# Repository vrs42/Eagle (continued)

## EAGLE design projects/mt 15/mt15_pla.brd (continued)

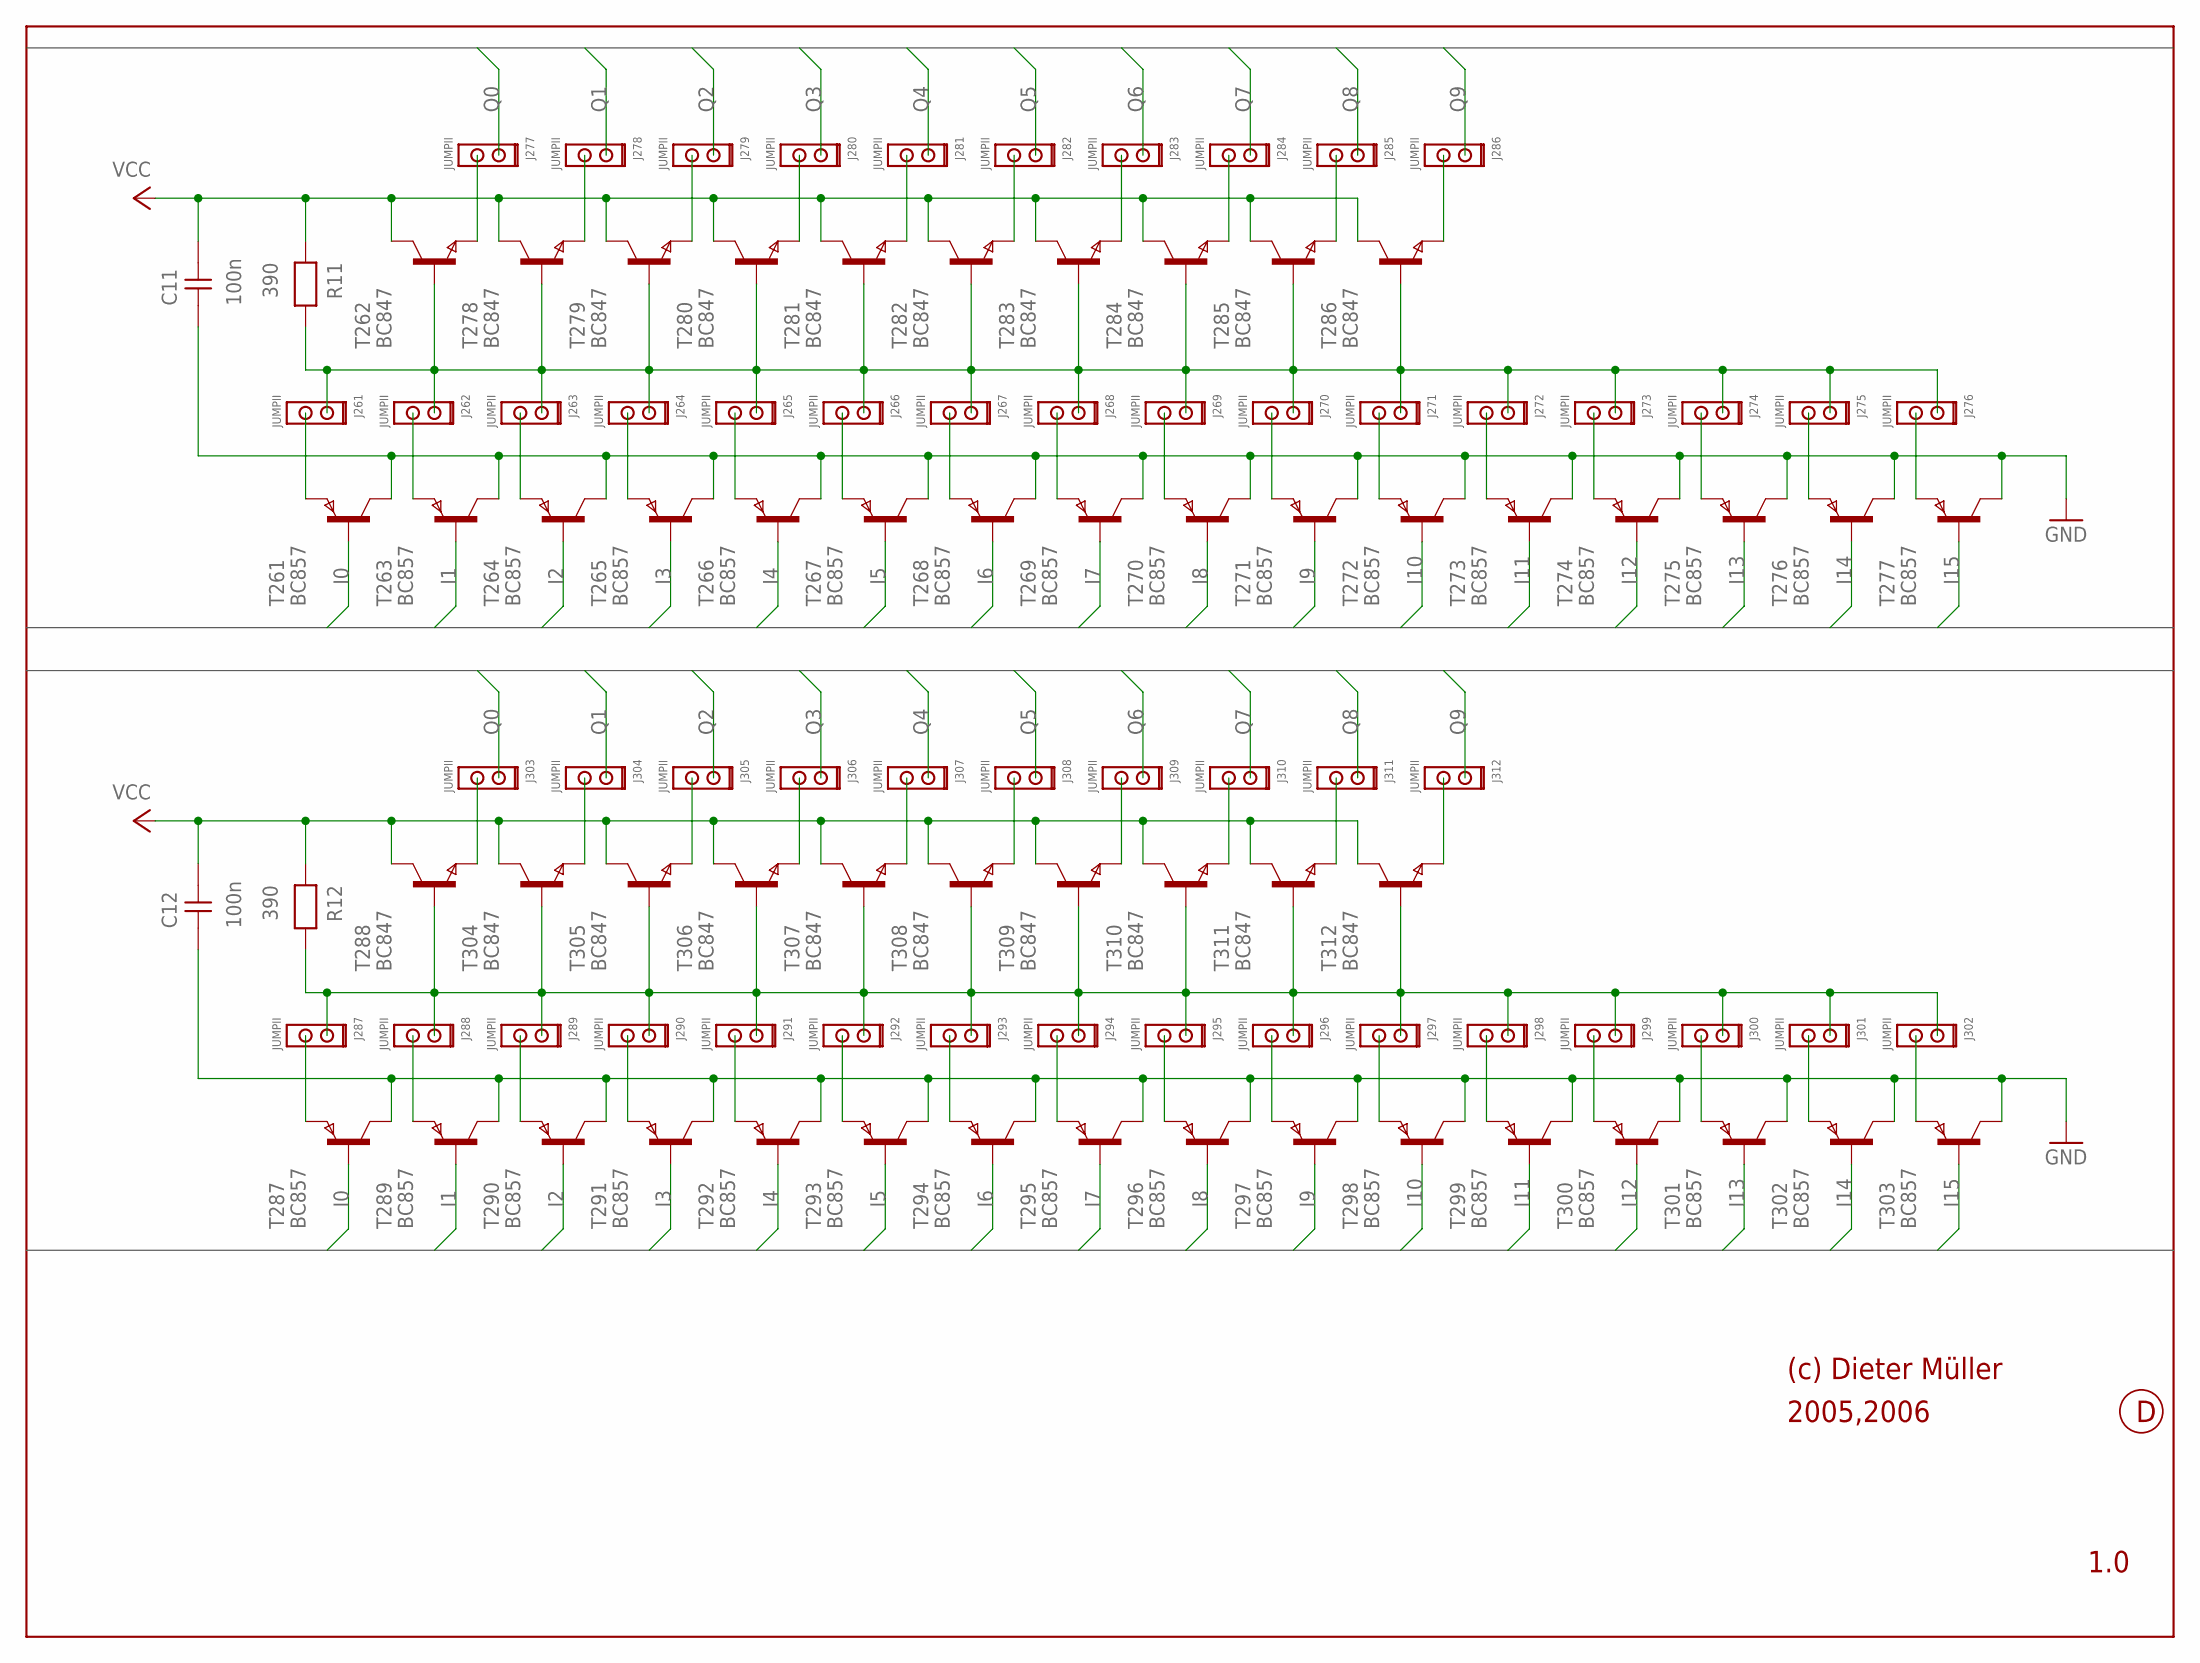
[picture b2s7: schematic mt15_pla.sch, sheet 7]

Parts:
C11, C12: 100n; 0204
J261, J262, J263, J264, J265, J266, J267, J268, J269, J270, J271, J272, J273, J274, J275, J276, J277, J278, J279, J280, J281, J282, J283, J284, J285, J286, J287, J288, J289, J290, J291, J292, J293, J294, J295, J296, J297, J298, J299, J300, J301, J302, J303, J304, J305, J306, J307, J308, J309, J310, J311, J312: JUMPII
R11, R12: 390; 0204
T261, T263, T264, T265, T266, T267, T268, T269, T270, T271, T272, T273, T274, T275, T276, T277, T287, T289, T290, T291, T292, T293, T294, T295, T296, T297, T298, T299, T300, T301, T302, T303: BC857; SOT-23
T262, T278, T279, T280, T281, T282, T283, T284, T285, T286, T288, T304, T305, T306, T307, T308, T309, T310, T311, T312: BC847; SOT-23

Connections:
GND: C11.1, C12.1, T261.3 (C), T263.3 (C), T264.3 (C), T265.3 (C), T266.3 (C), T267.3 (C), T268.3 (C), T269.3 (C), T270.3 (C), T271.3 (C), T272.3 (C), T273.3 (C), T274.3 (C), T275.3 (C), T276.3 (C), T277.3 (C), T287.3 (C), T289.3 (C), T290.3 (C), T291.3 (C), T292.3 (C), T293.3 (C), T294.3 (C), T295.3 (C), T296.3 (C), T297.3 (C), T298.3 (C), T299.3 (C), T300.3 (C), T301.3 (C), T302.3 (C), T303.3 (C); also elsewhere on the board
I0: T261.2 (B), T287.2 (B); also elsewhere on the board
I1: T263.2 (B), T289.2 (B); also elsewhere on the board
I2: T264.2 (B), T290.2 (B); also elsewhere on the board
I3: T265.2 (B), T291.2 (B); also elsewhere on the board
I4: T266.2 (B), T292.2 (B); also elsewhere on the board
I5: T267.2 (B), T293.2 (B); also elsewhere on the board
I6: T268.2 (B), T294.2 (B); also elsewhere on the board
I7: T269.2 (B), T295.2 (B); also elsewhere on the board
I8: T270.2 (B), T296.2 (B); also elsewhere on the board
I9: T271.2 (B), T297.2 (B); also elsewhere on the board
I10: T272.2 (B), T298.2 (B); also elsewhere on the board
I11: T273.2 (B), T299.2 (B); also elsewhere on the board
I12: T274.2 (B), T300.2 (B); also elsewhere on the board
I13: T275.2 (B), T301.2 (B); also elsewhere on the board
I14: T276.2 (B), T302.2 (B); also elsewhere on the board
I15: T277.2 (B), T303.2 (B); also elsewhere on the board
unnamed: J261.2, T261.1 (E)
unnamed: J262.2, T263.1 (E)
unnamed: J263.2, T264.1 (E)
unnamed: J261.1, J262.1, J263.1, J264.1, J265.1, J266.1, J267.1, J268.1, J269.1, J270.1, J271.1, J272.1, J273.1, J274.1, J275.1, J276.1, R11.2, T262.2 (B), T278.2 (B), T279.2 (B), T280.2 (B), T281.2 (B), T282.2 (B), T283.2 (B), T284.2 (B), T285.2 (B), T286.2 (B)
unnamed: J276.2, T277.1 (E)
unnamed: J275.2, T276.1 (E)
unnamed: J274.2, T275.1 (E)
unnamed: J273.2, T274.1 (E)
unnamed: J272.2, T273.1 (E)
unnamed: J266.2, T267.1 (E)
unnamed: J265.2, T266.1 (E)
unnamed: J264.2, T265.1 (E)
unnamed: J267.2, T268.1 (E)
unnamed: J268.2, T269.1 (E)
unnamed: J269.2, T270.1 (E)
unnamed: J270.2, T271.1 (E)
unnamed: J271.2, T272.1 (E)
unnamed: J286.2, T286.1 (E)
unnamed: J277.2, T262.1 (E)
unnamed: J278.2, T278.1 (E)
unnamed: J279.2, T279.1 (E)
unnamed: J280.2, T280.1 (E)
unnamed: J281.2, T281.1 (E)
unnamed: J282.2, T282.1 (E)
unnamed: J283.2, T283.1 (E)
unnamed: J284.2, T284.1 (E)
unnamed: J285.2, T285.1 (E)
unnamed: J287.2, T287.1 (E)
unnamed: J288.2, T289.1 (E)
unnamed: J289.2, T290.1 (E)
unnamed: J287.1, J288.1, J289.1, J290.1, J291.1, J292.1, J293.1, J294.1, J295.1, J296.1, J297.1, J298.1, J299.1, J300.1, J301.1, J302.1, R12.2, T288.2 (B), T304.2 (B), T305.2 (B), T306.2 (B), T307.2 (B), T308.2 (B), T309.2 (B), T310.2 (B), T311.2 (B), T312.2 (B)
unnamed: J302.2, T303.1 (E)
unnamed: J301.2, T302.1 (E)
unnamed: J300.2, T301.1 (E)
unnamed: J299.2, T300.1 (E)
unnamed: J298.2, T299.1 (E)
unnamed: J292.2, T293.1 (E)
unnamed: J291.2, T292.1 (E)
unnamed: J290.2, T291.1 (E)
unnamed: J293.2, T294.1 (E)
unnamed: J294.2, T295.1 (E)
unnamed: J295.2, T296.1 (E)
unnamed: J296.2, T297.1 (E)
unnamed: J297.2, T298.1 (E)
unnamed: J312.2, T312.1 (E)
unnamed: J303.2, T288.1 (E)
unnamed: J304.2, T304.1 (E)
unnamed: J305.2, T305.1 (E)
unnamed: J306.2, T306.1 (E)
unnamed: J307.2, T307.1 (E)
unnamed: J308.2, T308.1 (E)
unnamed: J309.2, T309.1 (E)
unnamed: J310.2, T310.1 (E)
unnamed: J311.2, T311.1 (E)
Q0: J277.1, J303.1; also elsewhere on the board
Q1: J278.1, J304.1; also elsewhere on the board
Q2: J279.1, J305.1; also elsewhere on the board
Q3: J280.1, J306.1; also elsewhere on the board
Q4: J281.1, J307.1; also elsewhere on the board
Q5: J282.1, J308.1; also elsewhere on the board
Q6: J283.1, J309.1; also elsewhere on the board
Q7: J284.1, J310.1; also elsewhere on the board
Q8: J285.1, J311.1; also elsewhere on the board
Q9: J286.1, J312.1; also elsewhere on the board
VCC: C11.2, C12.2, R11.1, R12.1, T262.3 (C), T278.3 (C), T279.3 (C), T280.3 (C), T281.3 (C), T282.3 (C), T283.3 (C), T284.3 (C), T285.3 (C), T286.3 (C), T288.3 (C), T304.3 (C), T305.3 (C), T306.3 (C), T307.3 (C), T308.3 (C), T309.3 (C), T310.3 (C), T311.3 (C), T312.3 (C); also elsewhere on the board

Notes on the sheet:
(c) Dieter Müller
2005,2006
1.0

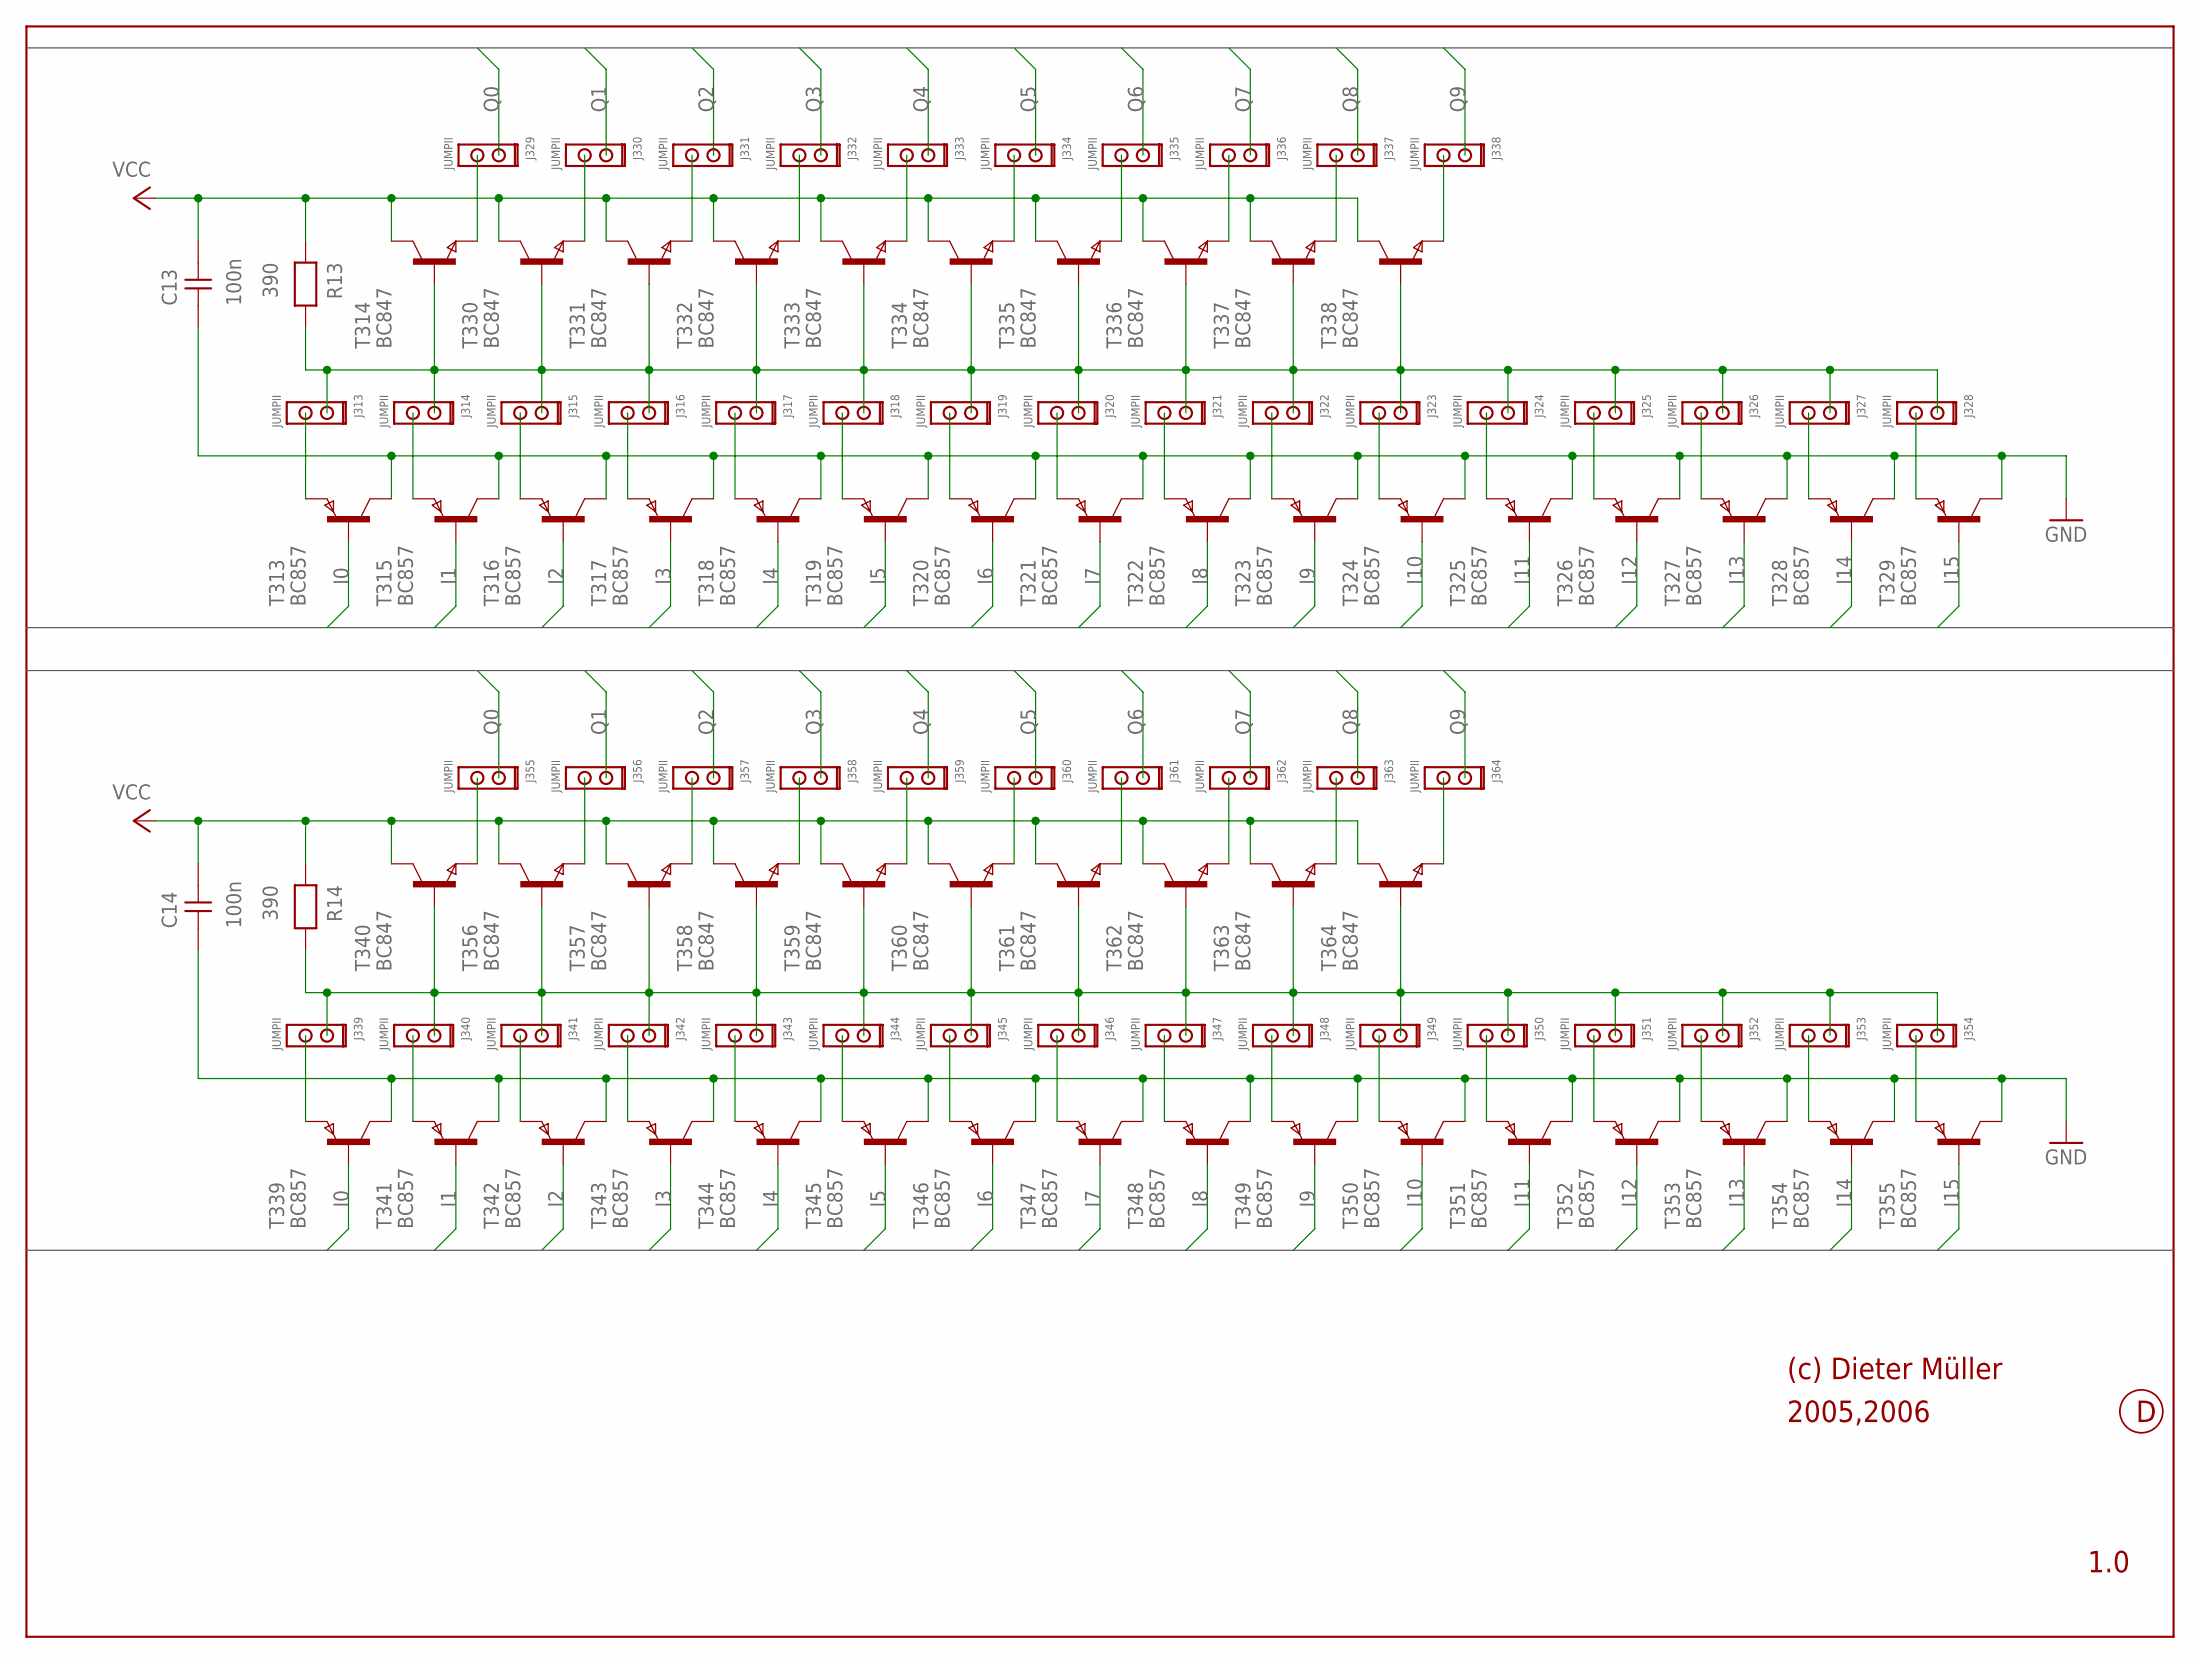
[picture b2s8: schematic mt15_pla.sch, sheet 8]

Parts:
C13, C14: 100n; 0204
J313, J314, J315, J316, J317, J318, J319, J320, J321, J322, J323, J324, J325, J326, J327, J328, J329, J330, J331, J332, J333, J334, J335, J336, J337, J338, J339, J340, J341, J342, J343, J344, J345, J346, J347, J348, J349, J350, J351, J352, J353, J354, J355, J356, J357, J358, J359, J360, J361, J362, J363, J364: JUMPII
R13, R14: 390; 0204
T313, T315, T316, T317, T318, T319, T320, T321, T322, T323, T324, T325, T326, T327, T328, T329, T339, T341, T342, T343, T344, T345, T346, T347, T348, T349, T350, T351, T352, T353, T354, T355: BC857; SOT-23
T314, T330, T331, T332, T333, T334, T335, T336, T337, T338, T340, T356, T357, T358, T359, T360, T361, T362, T363, T364: BC847; SOT-23

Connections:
GND: C13.1, C14.1, T313.3 (C), T315.3 (C), T316.3 (C), T317.3 (C), T318.3 (C), T319.3 (C), T320.3 (C), T321.3 (C), T322.3 (C), T323.3 (C), T324.3 (C), T325.3 (C), T326.3 (C), T327.3 (C), T328.3 (C), T329.3 (C), T339.3 (C), T341.3 (C), T342.3 (C), T343.3 (C), T344.3 (C), T345.3 (C), T346.3 (C), T347.3 (C), T348.3 (C), T349.3 (C), T350.3 (C), T351.3 (C), T352.3 (C), T353.3 (C), T354.3 (C), T355.3 (C); also elsewhere on the board
I0: T313.2 (B), T339.2 (B); also elsewhere on the board
I1: T315.2 (B), T341.2 (B); also elsewhere on the board
I2: T316.2 (B), T342.2 (B); also elsewhere on the board
I3: T317.2 (B), T343.2 (B); also elsewhere on the board
I4: T318.2 (B), T344.2 (B); also elsewhere on the board
I5: T319.2 (B), T345.2 (B); also elsewhere on the board
I6: T320.2 (B), T346.2 (B); also elsewhere on the board
I7: T321.2 (B), T347.2 (B); also elsewhere on the board
I8: T322.2 (B), T348.2 (B); also elsewhere on the board
I9: T323.2 (B), T349.2 (B); also elsewhere on the board
I10: T324.2 (B), T350.2 (B); also elsewhere on the board
I11: T325.2 (B), T351.2 (B); also elsewhere on the board
I12: T326.2 (B), T352.2 (B); also elsewhere on the board
I13: T327.2 (B), T353.2 (B); also elsewhere on the board
I14: T328.2 (B), T354.2 (B); also elsewhere on the board
I15: T329.2 (B), T355.2 (B); also elsewhere on the board
unnamed: J313.2, T313.1 (E)
unnamed: J314.2, T315.1 (E)
unnamed: J315.2, T316.1 (E)
unnamed: J313.1, J314.1, J315.1, J316.1, J317.1, J318.1, J319.1, J320.1, J321.1, J322.1, J323.1, J324.1, J325.1, J326.1, J327.1, J328.1, R13.2, T314.2 (B), T330.2 (B), T331.2 (B), T332.2 (B), T333.2 (B), T334.2 (B), T335.2 (B), T336.2 (B), T337.2 (B), T338.2 (B)
unnamed: J328.2, T329.1 (E)
unnamed: J327.2, T328.1 (E)
unnamed: J326.2, T327.1 (E)
unnamed: J325.2, T326.1 (E)
unnamed: J324.2, T325.1 (E)
unnamed: J318.2, T319.1 (E)
unnamed: J317.2, T318.1 (E)
unnamed: J316.2, T317.1 (E)
unnamed: J319.2, T320.1 (E)
unnamed: J320.2, T321.1 (E)
unnamed: J321.2, T322.1 (E)
unnamed: J322.2, T323.1 (E)
unnamed: J323.2, T324.1 (E)
unnamed: J338.2, T338.1 (E)
unnamed: J329.2, T314.1 (E)
unnamed: J330.2, T330.1 (E)
unnamed: J331.2, T331.1 (E)
unnamed: J332.2, T332.1 (E)
unnamed: J333.2, T333.1 (E)
unnamed: J334.2, T334.1 (E)
unnamed: J335.2, T335.1 (E)
unnamed: J336.2, T336.1 (E)
unnamed: J337.2, T337.1 (E)
unnamed: J339.2, T339.1 (E)
unnamed: J340.2, T341.1 (E)
unnamed: J341.2, T342.1 (E)
unnamed: J339.1, J340.1, J341.1, J342.1, J343.1, J344.1, J345.1, J346.1, J347.1, J348.1, J349.1, J350.1, J351.1, J352.1, J353.1, J354.1, R14.2, T340.2 (B), T356.2 (B), T357.2 (B), T358.2 (B), T359.2 (B), T360.2 (B), T361.2 (B), T362.2 (B), T363.2 (B), T364.2 (B)
unnamed: J354.2, T355.1 (E)
unnamed: J353.2, T354.1 (E)
unnamed: J352.2, T353.1 (E)
unnamed: J351.2, T352.1 (E)
unnamed: J350.2, T351.1 (E)
unnamed: J344.2, T345.1 (E)
unnamed: J343.2, T344.1 (E)
unnamed: J342.2, T343.1 (E)
unnamed: J345.2, T346.1 (E)
unnamed: J346.2, T347.1 (E)
unnamed: J347.2, T348.1 (E)
unnamed: J348.2, T349.1 (E)
unnamed: J349.2, T350.1 (E)
unnamed: J364.2, T364.1 (E)
unnamed: J355.2, T340.1 (E)
unnamed: J356.2, T356.1 (E)
unnamed: J357.2, T357.1 (E)
unnamed: J358.2, T358.1 (E)
unnamed: J359.2, T359.1 (E)
unnamed: J360.2, T360.1 (E)
unnamed: J361.2, T361.1 (E)
unnamed: J362.2, T362.1 (E)
unnamed: J363.2, T363.1 (E)
Q0: J329.1, J355.1; also elsewhere on the board
Q1: J330.1, J356.1; also elsewhere on the board
Q2: J331.1, J357.1; also elsewhere on the board
Q3: J332.1, J358.1; also elsewhere on the board
Q4: J333.1, J359.1; also elsewhere on the board
Q5: J334.1, J360.1; also elsewhere on the board
Q6: J335.1, J361.1; also elsewhere on the board
Q7: J336.1, J362.1; also elsewhere on the board
Q8: J337.1, J363.1; also elsewhere on the board
Q9: J338.1, J364.1; also elsewhere on the board
VCC: C13.2, C14.2, R13.1, R14.1, T314.3 (C), T330.3 (C), T331.3 (C), T332.3 (C), T333.3 (C), T334.3 (C), T335.3 (C), T336.3 (C), T337.3 (C), T338.3 (C), T340.3 (C), T356.3 (C), T357.3 (C), T358.3 (C), T359.3 (C), T360.3 (C), T361.3 (C), T362.3 (C), T363.3 (C), T364.3 (C); also elsewhere on the board

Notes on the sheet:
(c) Dieter Müller
2005,2006
1.0

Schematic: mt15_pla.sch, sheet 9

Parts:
C15, C16: 100n; 0204
J365, J366, J367, J368, J369, J370, J371, J372, J373, J374, J375, J376, J377, J378, J379, J380, J381, J382, J383, J384, J385, J386, J387, J388, J389, J390, J391, J392, J393, J394, J395, J396, J397, J398, J399, J400, J401, J402, J403, J404, J405, J406, J407, J408, J409, J410, J411, J412, J413, J414, J415, J416: JUMPII
R15, R16: 390; 0204
T365, T367, T368, T369, T370, T371, T372, T373, T374, T375, T376, T377, T378, T379, T380, T381, T391, T393, T394, T395, T396, T397, T398, T399, T400, T401, T402, T403, T404, T405, T406, T407: BC857; SOT-23
T366, T382, T383, T384, T385, T386, T387, T388, T389, T390, T392, T408, T409, T410, T411, T412, T413, T414, T415, T416: BC847; SOT-23

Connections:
GND: C15.1, C16.1, T365.3 (C), T367.3 (C), T368.3 (C), T369.3 (C), T370.3 (C), T371.3 (C), T372.3 (C), T373.3 (C), T374.3 (C), T375.3 (C), T376.3 (C), T377.3 (C), T378.3 (C), T379.3 (C), T380.3 (C), T381.3 (C), T391.3 (C), T393.3 (C), T394.3 (C), T395.3 (C), T396.3 (C), T397.3 (C), T398.3 (C), T399.3 (C), T400.3 (C), T401.3 (C), T402.3 (C), T403.3 (C), T404.3 (C), T405.3 (C), T406.3 (C), T407.3 (C); also elsewhere on the board
I0: T365.2 (B), T391.2 (B); also elsewhere on the board
I1: T367.2 (B), T393.2 (B); also elsewhere on the board
I2: T368.2 (B), T394.2 (B); also elsewhere on the board
I3: T369.2 (B), T395.2 (B); also elsewhere on the board
I4: T370.2 (B), T396.2 (B); also elsewhere on the board
I5: T371.2 (B), T397.2 (B); also elsewhere on the board
I6: T372.2 (B), T398.2 (B); also elsewhere on the board
I7: T373.2 (B), T399.2 (B); also elsewhere on the board
I8: T374.2 (B), T400.2 (B); also elsewhere on the board
I9: T375.2 (B), T401.2 (B); also elsewhere on the board
I10: T376.2 (B), T402.2 (B); also elsewhere on the board
I11: T377.2 (B), T403.2 (B); also elsewhere on the board
I12: T378.2 (B), T404.2 (B); also elsewhere on the board
I13: T379.2 (B), T405.2 (B); also elsewhere on the board
I14: T380.2 (B), T406.2 (B); also elsewhere on the board
I15: T381.2 (B), T407.2 (B); also elsewhere on the board
unnamed: J365.2, T365.1 (E)
unnamed: J366.2, T367.1 (E)
unnamed: J367.2, T368.1 (E)
unnamed: J365.1, J366.1, J367.1, J368.1, J369.1, J370.1, J371.1, J372.1, J373.1, J374.1, J375.1, J376.1, J377.1, J378.1, J379.1, J380.1, R15.2, T366.2 (B), T382.2 (B), T383.2 (B), T384.2 (B), T385.2 (B), T386.2 (B), T387.2 (B), T388.2 (B), T389.2 (B), T390.2 (B)
unnamed: J380.2, T381.1 (E)
unnamed: J379.2, T380.1 (E)
unnamed: J378.2, T379.1 (E)
unnamed: J377.2, T378.1 (E)
unnamed: J376.2, T377.1 (E)
unnamed: J370.2, T371.1 (E)
unnamed: J369.2, T370.1 (E)
unnamed: J368.2, T369.1 (E)
unnamed: J371.2, T372.1 (E)
unnamed: J372.2, T373.1 (E)
unnamed: J373.2, T374.1 (E)
unnamed: J374.2, T375.1 (E)
unnamed: J375.2, T376.1 (E)
unnamed: J390.2, T390.1 (E)
unnamed: J381.2, T366.1 (E)
unnamed: J382.2, T382.1 (E)
unnamed: J383.2, T383.1 (E)
unnamed: J384.2, T384.1 (E)
unnamed: J385.2, T385.1 (E)
unnamed: J386.2, T386.1 (E)
unnamed: J387.2, T387.1 (E)
unnamed: J388.2, T388.1 (E)
unnamed: J389.2, T389.1 (E)
unnamed: J391.2, T391.1 (E)
unnamed: J392.2, T393.1 (E)
unnamed: J393.2, T394.1 (E)
unnamed: J391.1, J392.1, J393.1, J394.1, J395.1, J396.1, J397.1, J398.1, J399.1, J400.1, J401.1, J402.1, J403.1, J404.1, J405.1, J406.1, R16.2, T392.2 (B), T408.2 (B), T409.2 (B), T410.2 (B), T411.2 (B), T412.2 (B), T413.2 (B), T414.2 (B), T415.2 (B), T416.2 (B)
unnamed: J406.2, T407.1 (E)
unnamed: J405.2, T406.1 (E)
unnamed: J404.2, T405.1 (E)
unnamed: J403.2, T404.1 (E)
unnamed: J402.2, T403.1 (E)
unnamed: J396.2, T397.1 (E)
unnamed: J395.2, T396.1 (E)
unnamed: J394.2, T395.1 (E)
unnamed: J397.2, T398.1 (E)
unnamed: J398.2, T399.1 (E)
unnamed: J399.2, T400.1 (E)
unnamed: J400.2, T401.1 (E)
unnamed: J401.2, T402.1 (E)
unnamed: J416.2, T416.1 (E)
unnamed: J407.2, T392.1 (E)
unnamed: J408.2, T408.1 (E)
unnamed: J409.2, T409.1 (E)
unnamed: J410.2, T410.1 (E)
unnamed: J411.2, T411.1 (E)
unnamed: J412.2, T412.1 (E)
unnamed: J413.2, T413.1 (E)
unnamed: J414.2, T414.1 (E)
unnamed: J415.2, T415.1 (E)
Q0: J381.1, J407.1; also elsewhere on the board
Q1: J382.1, J408.1; also elsewhere on the board
Q2: J383.1, J409.1; also elsewhere on the board
Q3: J384.1, J410.1; also elsewhere on the board
Q4: J385.1, J411.1; also elsewhere on the board
Q5: J386.1, J412.1; also elsewhere on the board
Q6: J387.1, J413.1; also elsewhere on the board
Q7: J388.1, J414.1; also elsewhere on the board
Q8: J389.1, J415.1; also elsewhere on the board
Q9: J390.1, J416.1; also elsewhere on the board
VCC: C15.2, C16.2, R15.1, R16.1, T366.3 (C), T382.3 (C), T383.3 (C), T384.3 (C), T385.3 (C), T386.3 (C), T387.3 (C), T388.3 (C), T389.3 (C), T390.3 (C), T392.3 (C), T408.3 (C), T409.3 (C), T410.3 (C), T411.3 (C), T412.3 (C), T413.3 (C), T414.3 (C), T415.3 (C), T416.3 (C); also elsewhere on the board

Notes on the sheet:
(c) Dieter Müller
2005,2006
1.0

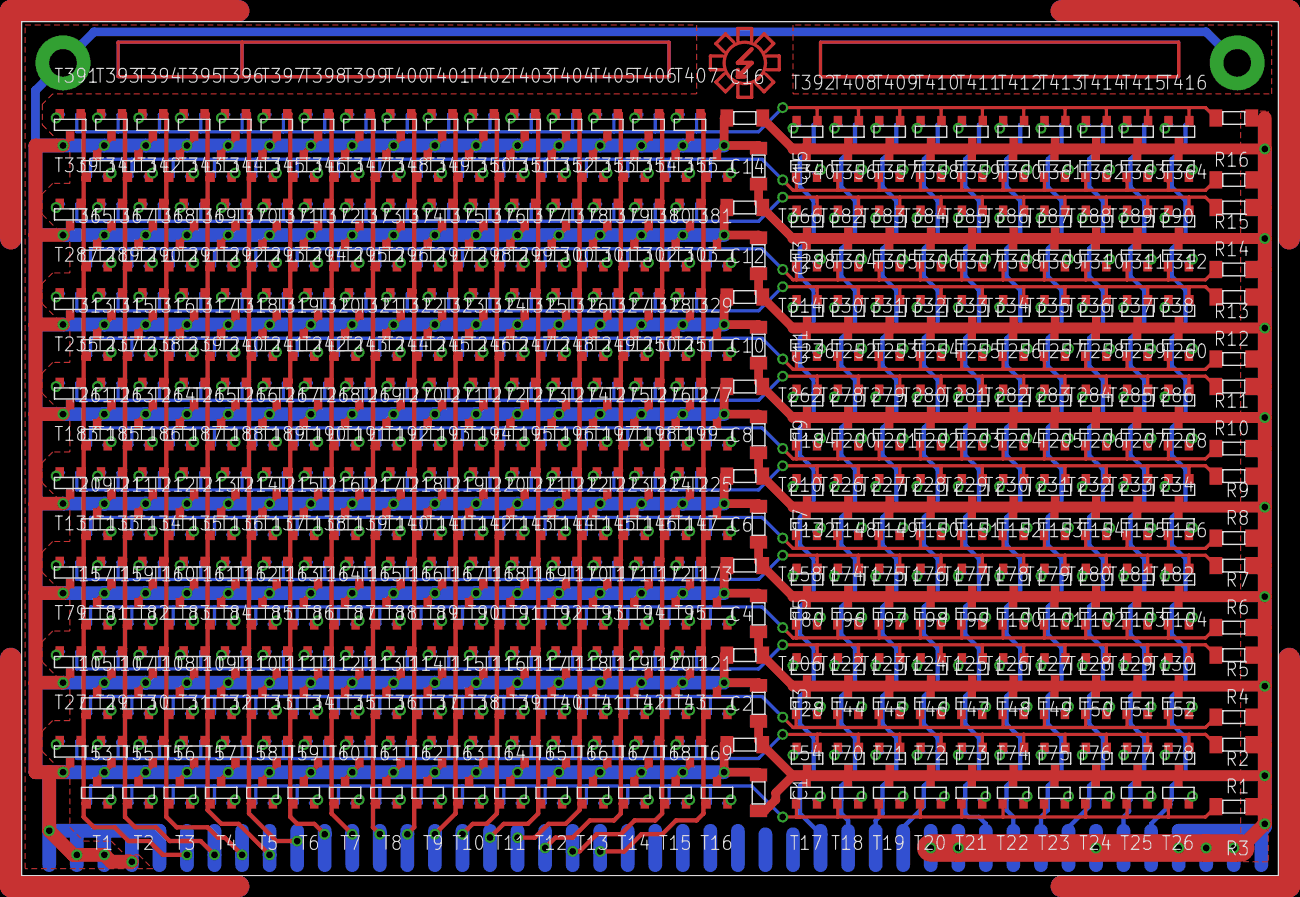
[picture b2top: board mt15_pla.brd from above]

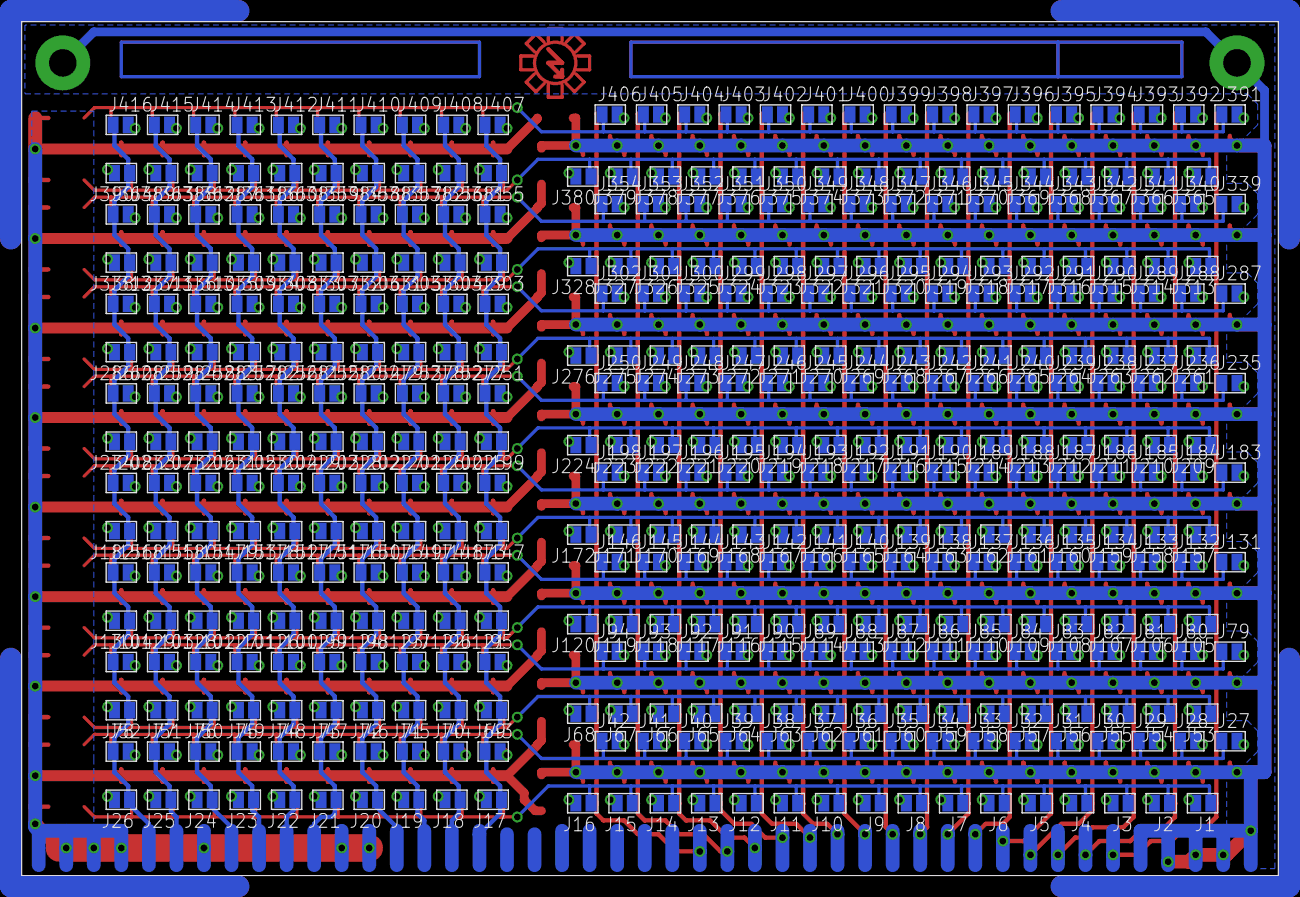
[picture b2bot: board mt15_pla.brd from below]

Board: 2 copper layers, 115.9 x 78.7 mm, 865 parts (416 on the bottom side), 460 nets.

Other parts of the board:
U$41: T1

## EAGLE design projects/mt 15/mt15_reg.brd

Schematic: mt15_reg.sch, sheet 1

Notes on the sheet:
(c) Dieter Müller
2005,2006
1.0
Free for hobby use, but probably not free of errors.
Provided as is , without any warranty or support.
Good luck.
ACC
L_ACC
I_ACC
ALU_A
O_ACC
I_PC
L_PC
O_PC
ALU_PC
L_T0
L_T1
ALU_Q0
ALU_Q1
OD_T0
OA_T0
OQ_T0
OD_T1
OA_T1
OQ_T1
Q_OUT
A_OUT
D_OUT
Address
Data
ALU
Note:
Blue marked lines
are outside of this module.
Green marked lines
work as control lines
(load or output_enable)
Block diagram
Supply voltage is 2.5V. Please change/modify resistors for other supply voltages.
For more details about the registers, consult the last page of this schematic (Page 6).

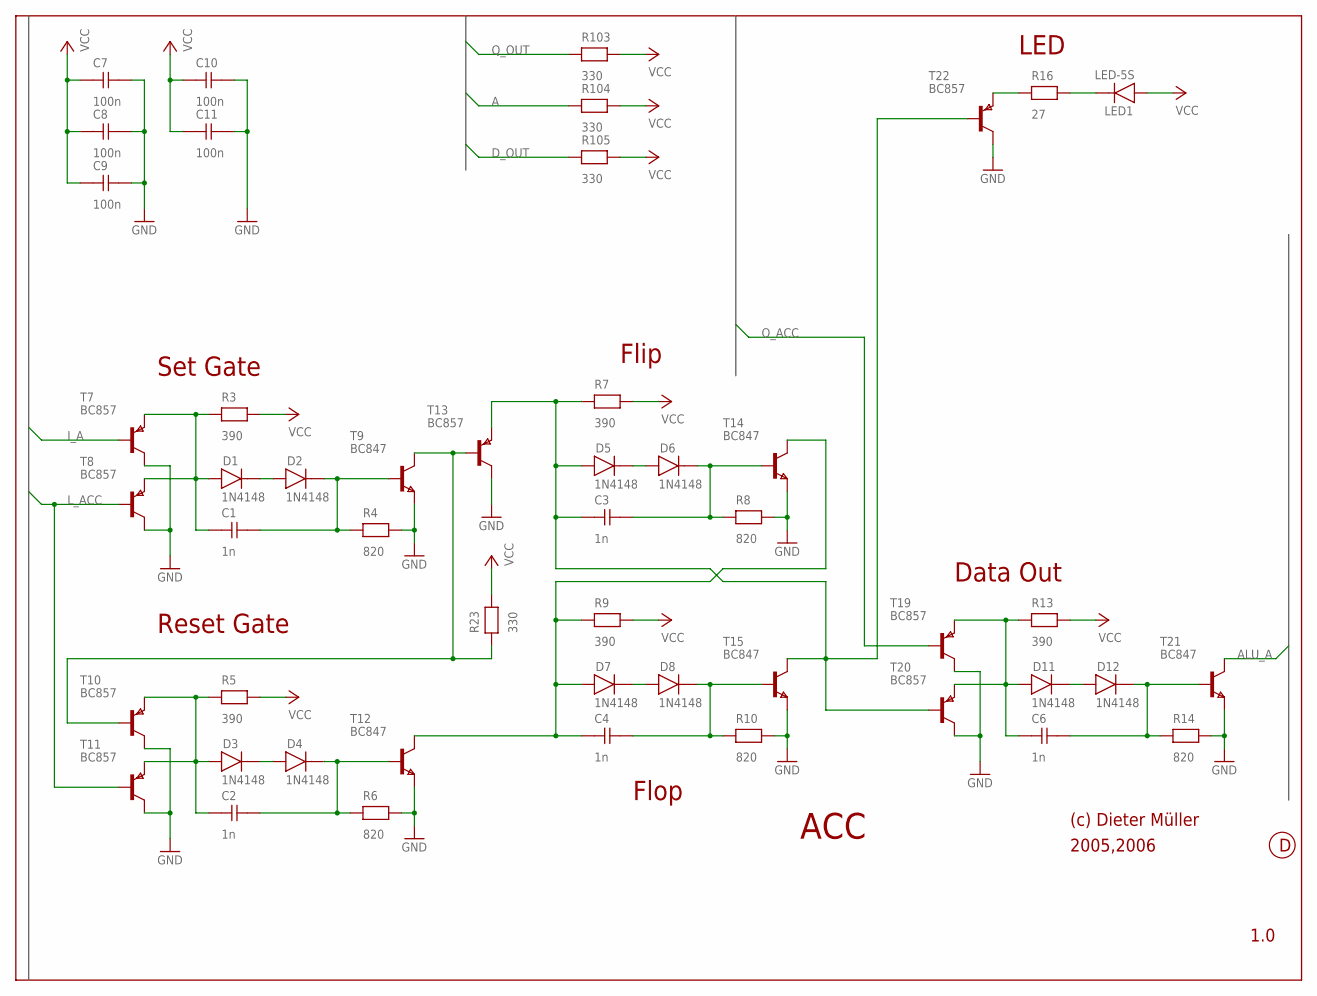
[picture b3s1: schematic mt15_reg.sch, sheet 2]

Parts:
C1, C2, C3, C4, C6: 1n; 0204
C7, C8, C9, C10, C11: 100n; 0204
D1, D2, D3, D4, D5, D6, D7, D8, D11, D12: 1N4148; 0204D
LED1: LED-5S
R3, R5, R7, R9, R13: 390; 0204
R4, R6, R8, R10, R14: 820; 0204
R16: 27; 0204
R23, R103, R104, R105: 330; 0204
T7, T8, T10, T11, T13, T19, T20, T22: BC857; SOT-23
T9, T12, T14, T15, T21: BC847; SOT-23

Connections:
A: R104.1; also elsewhere on the board
ALU_A: T21.3 (C)
D_OUT: R105.1; also elsewhere on the board
GND: C7.2, C8.2, C9.2, C10.2, C11.2, R4.2, R6.2, R8.2, R10.2, R14.2, T7.3 (C), T8.3 (C), T9.1 (E), T10.3 (C), T11.3 (C), T12.1 (E), T13.3 (C), T14.1 (E), T15.1 (E), T19.3 (C), T20.3 (C), T21.1 (E), T22.3 (C); also elsewhere on the board
I_A: T7.2 (B)
L_ACC: T8.2 (B), T11.2 (B)
unnamed: C1.1, D1.1 (A), R3.1, T7.1 (E), T8.1 (E)
unnamed: D1.2 (K), D2.1 (A)
unnamed: C1.2, D2.2 (K), R4.1, T9.2 (B)
unnamed: D5.2 (K), D6.1 (A)
unnamed: C2.1, D3.1 (A), R5.1, T10.1 (E), T11.1 (E)
unnamed: D3.2 (K), D4.1 (A)
unnamed: C2.2, D4.2 (K), R6.1, T12.2 (B)
unnamed: C3.2, D6.2 (K), R8.1, T14.2 (B)
unnamed: D7.2 (K), D8.1 (A)
unnamed: C4.2, D8.2 (K), R10.1, T15.2 (B)
unnamed: C4.1, D7.1 (A), R9.1, T12.3 (C), T14.3 (C)
unnamed: C3.1, D5.1 (A), R7.1, T13.1 (E), T15.3 (C), T20.2 (B), T22.2 (B)
unnamed: R16.1, T22.1 (E)
unnamed: LED1.2 (K), R16.2
unnamed: C6.1, D11.1 (A), R13.1, T19.1 (E), T20.1 (E)
unnamed: D11.2 (K), D12.1 (A)
unnamed: C6.2, D12.2 (K), R14.1, T21.2 (B)
unnamed: R23.1, T9.3 (C), T10.2 (B), T13.2 (B)
O_ACC: T19.2 (B)
Q_OUT: R103.1; also elsewhere on the board
VCC: C7.1, C8.1, C9.1, C10.1, C11.1, LED1.1 (A), R3.2, R5.2, R7.2, R9.2, R13.2, R23.2, R103.2, R104.2, R105.2; also elsewhere on the board

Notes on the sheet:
Set Gate
Reset Gate
Flip
Flop
Data Out
LED
(c) Dieter Müller
2005,2006
1.0
ACC
